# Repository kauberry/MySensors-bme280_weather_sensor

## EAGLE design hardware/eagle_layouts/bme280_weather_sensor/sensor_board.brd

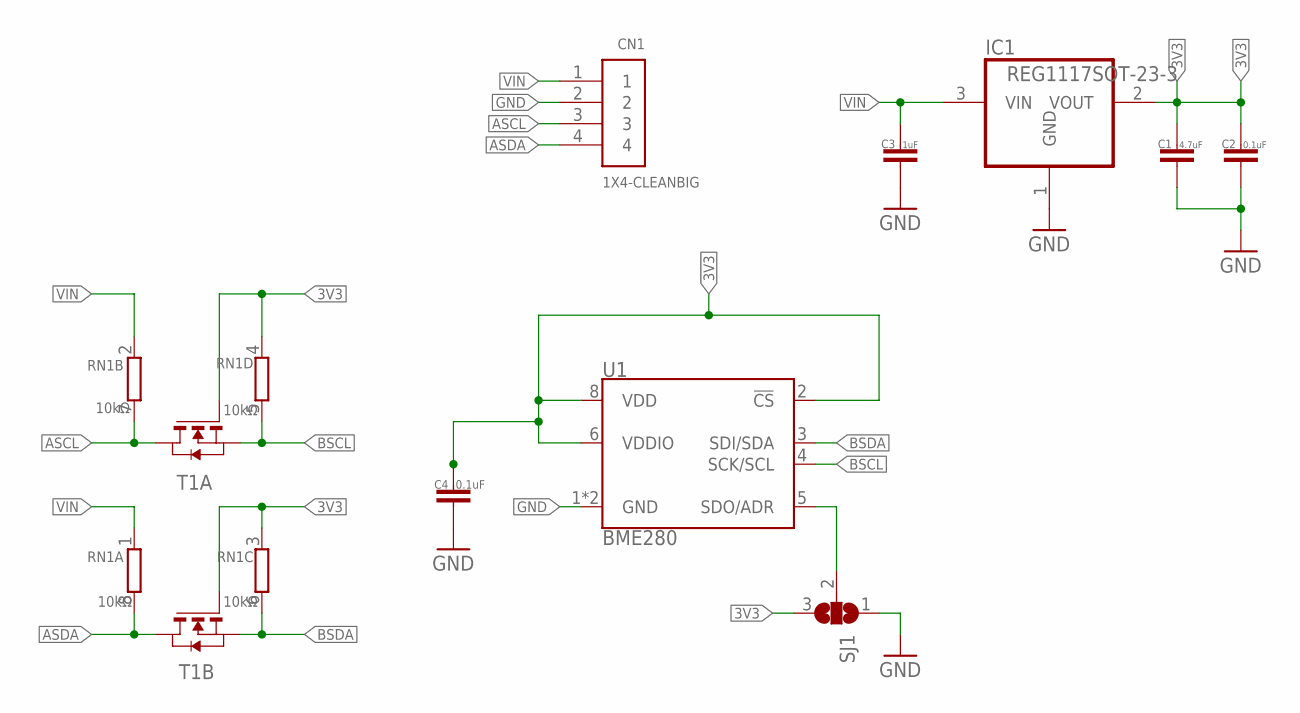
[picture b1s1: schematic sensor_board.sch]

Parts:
C1: 4.7uF; C0603
C2, C4: 0.1uF; C0603
C3: 1uF; C0603
CN1: 1X4-CLEANBIG; 1X04-CLEANBIG
IC1: REG1117SOT-23-3; SOT23-3
RN1: 10kΩ; EXB38V
SJ1: SJ2W; SJ_2
T1: ZXMD63N03XSOT-363; SOT-363
U1: BME280; LGA-8-2.5X2.5

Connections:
3V3: C1.1, C2.1, C4.1, IC1.2 (VOUT), RN1.3 (1), RN1.4 (1), SJ1.3, T1.2 (G), T1.5 (G), U1.2 (!CS), U1.6 (VDDIO), U1.8 (VDD)
ASCL: CN1.3, RN1.7 (2), T1.6 (D)
ASDA: CN1.4, RN1.8 (2), T1.3 (D)
BSCL: RN1.5 (2), T1.1 (S), U1.4 (SCK/SCL)
BSDA: RN1.6 (2), T1.4 (S), U1.3 (SDI/SDA)
GND: C1.2, C2.2, C3.2, C4.2, CN1.2, IC1.1 (GND), SJ1.1, U1.1 (GND), U1.7 (GND)
unnamed: SJ1.2, U1.5 (SDO/ADR)
VIN: C3.1, CN1.1, IC1.3 (VIN), RN1.1, RN1.2 (1)

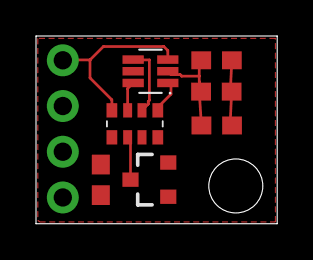
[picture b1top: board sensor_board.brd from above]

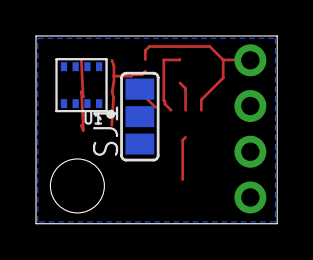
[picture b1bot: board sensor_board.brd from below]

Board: 2 copper layers, 13.4 x 10.4 mm, 10 parts (2 on the bottom side), 8 nets.

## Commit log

2018-04-30 Initial hardware designs commit
2018-05-02 Starting board layout for BME280 breakout
2019-07-22 Interim version

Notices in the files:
parts and their libraries:
SparkFun-Sensors: Licensing: Creative Commons ShareAlike 4.0 International - https://creativecommons.org/licenses/by-sa/4.0
